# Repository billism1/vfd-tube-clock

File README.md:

# VFD Tube Clock

This project is a WiFi-connected clock that uses an IV-21 VFD (Vacuum Fluorescent Display) tube for the display and a custom PCB controlled by an ESP32 microcontroller. Built with PlatformIO using the Arduino framework, it should work with other ESP32 variants and Arduino-compatible MCUs.

## Design Overview

The PCB is designed around the Seeeduino ESP32-C3 devboard but can be adapted for other microcontrollers. The schematic and PCB design files were created using KiCad 9.0, with firmware development in VS Code with PlatformIO.

## Project Background

This is the first time I've had PCBs printed. I've been a software developer for many years and have been dabbling in electronics as a hobby over the past couple of years. I've been fascinated by vintage display technology - there's something captivating about the warm glow and classic look of old tube displays, plus those beautiful colors that display tubes like Nixie tubes and VFDs produce. I love the idea of bridging old and new technology by controlling these vintage displays with modern microcontrollers and WiFi connectivity.

**Current Status:** I'm actively refining the PCB design based on initial testing. The photos and videos below show the first prototype batch of 5 PCBs, while the KiCad files reflect ongoing improvements to the design.

## Project Photos

<div align="center">

</div>

## Web Interface

Though most of the source code I wrote myself, one of my weak areas is web UI design. I used an LLM (claude.ai) to generate a Soviet themed web UI for controlling the clock over WiFi. Soviet - because these IV-21 VFD tubes were manufactured in Soviet USSR.

**[View Web Interface Screenshots in images dir →](images/)**

## Video

*Click to watch the demo video*

## How VFD Tubes Work

VFDs use phosphor materials, typically zinc oxide (ZnO) doped with zinc sulfide or other compounds, that emit light when struck by electrons from a heated filament cathode. The phosphor coating on the anode segments converts the electron energy into visible light, usually producing a characteristic blue-green glow, though the exact color depends on the specific phosphor formulation. The IV-21 specifically uses a zinc-based phosphor that creates its distinctive aqua-blue appearance.

The electrical requirements involve multiple voltages: a low filament voltage to heat the cathode (~2.5V DC for the IV-21), and higher anode/grid voltages to accelerate electrons toward the phosphor-coated segments (typically ~27V DC for the IV-21).

Multiplexing is the key technique that makes multi-digit VFD clocks practical - instead of driving all digits simultaneously (which would require complex, expensive circuitry), we rapidly cycle through each digit position, lighting only one at a time. By switching between digits faster than your eye can detect (typically 100Hz or higher), each digit appears continuously lit even though it's only powered for a fraction of the time. This creates the illusion of a stable, solid display across all digits while dramatically simplifying the driver electronics.

## Key Circuit Design Components

### Voltage Booster Circuit
The VFD needs 27V but our power supply only provides 5V, so we need a boost converter to step up the voltage. This circuit works like a voltage pump - it stores energy in an inductor coil when a transistor switches on, then releases that energy at a higher voltage when the transistor switches off. A diode ensures the boosted voltage flows in the right direction, and the ESP32 generates the rapid on/off switching signal (PWM) that makes it all work.
The circuit takes our 5V input and pumps it up to the 27V needed by the MAX6921 driver chip, which then distributes power to light up the VFD segments.

### MAX6921 VFD Driver
The MAX6921 IC serves as the interface between the microcontroller and VFD tube. It receives 3 bytes of data from the ESP32 telling it which segments to illuminate, then distributes the boosted 27V to the appropriate pins at precise timing intervals for proper message display. Multiple MAX6921s can be chained together for tubes with more digits or multiple tubes.

## Software Features

### Core Functionality
- **WiFi Connectivity:** Automatic connection to configured network
- **NTP Time Sync:** Retrieves accurate time from "pool.ntp.org"
- **Web Server:** Built-in HTTP server for device control
- **Multiple Display Modes:**
  - Time display mode
  - Custom message mode
  - "Flash message" mode with glitchy visual effects

### Flash Message Mode
As a novelty feature (which can be disabled), the clock occasionally displays random words that appear to "glitch" into existence—brief flashes of random characters before settling on the final message for a brief period, creating a subliminal effect. The word selection (easily changed in code) and styling pay homage to the Soviet heritage of these VFD tubes.

## Planned Improvements

### Hardware Enhancements
- **Better Voltage Regulation**
- **Multi-digit Support:** Extend design for tubes with more digits (IV-27 with 13 digits)

### Software Features
- **Better Wifi Management:** Default to AP mode for after compilation WiFi configuration
- **Text Scrolling:** Support for messages longer than 8 characters
- **Smart PWM Control:** Implement PID algorithm for voltage regulation
- **Enhanced Web UI:** Additional control options and settings
- **Button Integration:** Assign meaningful functions to hardware buttons which are not programmed to do anything currently

## Acknowledgments

This project was heavily inspired by and references the excellent work of:

- **[Tiny IV-21 VFD Clock](https://hackaday.io/project/167749-tiny-iv-21-vfd-clock)** - Original design inspiration. At least this was the first similar project that I came across. Uses an Atmega328P microcontroller and external (to the microcontroller module) RTC (real-time clock) component.
- **[Tiny IV-21 VFD Clock with ESP32](https://hackaday.io/project/202799-tiny-iv-21-vfd-clock-with-esp32)** - ESP32 implementation inspired from the above mentioned "Tiny IV-21 VFD Clock" project. Excludes the external RTC component and uses WiFi/Internet for automatic time synchronization.

Special thanks to the creators of these projects for sharing their knowledge and making this hobby accessible to others.

## Project Organization

### Where to find stuff
- [Main board PCB KiCad design files](./pcb/main-board/)
- [Sub-board PCB (VFD tube holder) design files](./pcb/sub-board/)
- [Main board PCB gerber files (ready to print PCBs)](./pcb-fab/gerber-main-board/)
- [An interactive BOM (Bill of Materials) for the main board](./pcb-fab/gerber-main-board/bom/)
- [Sub-board PCB - VFD tube holder (ready to print PCBs)](./pcb-fab/gerber-sub-board/)
- [Source code](./firmware/) (Built with PlatformIO for simplified dependency management and cross-platform development)

## License

This project is licensed under the MIT License - see the [LICENSE](LICENSE) file for details.

## Contributing

Contributions are welcome! Please feel free to submit pull requests or open issues for bugs and feature requests.

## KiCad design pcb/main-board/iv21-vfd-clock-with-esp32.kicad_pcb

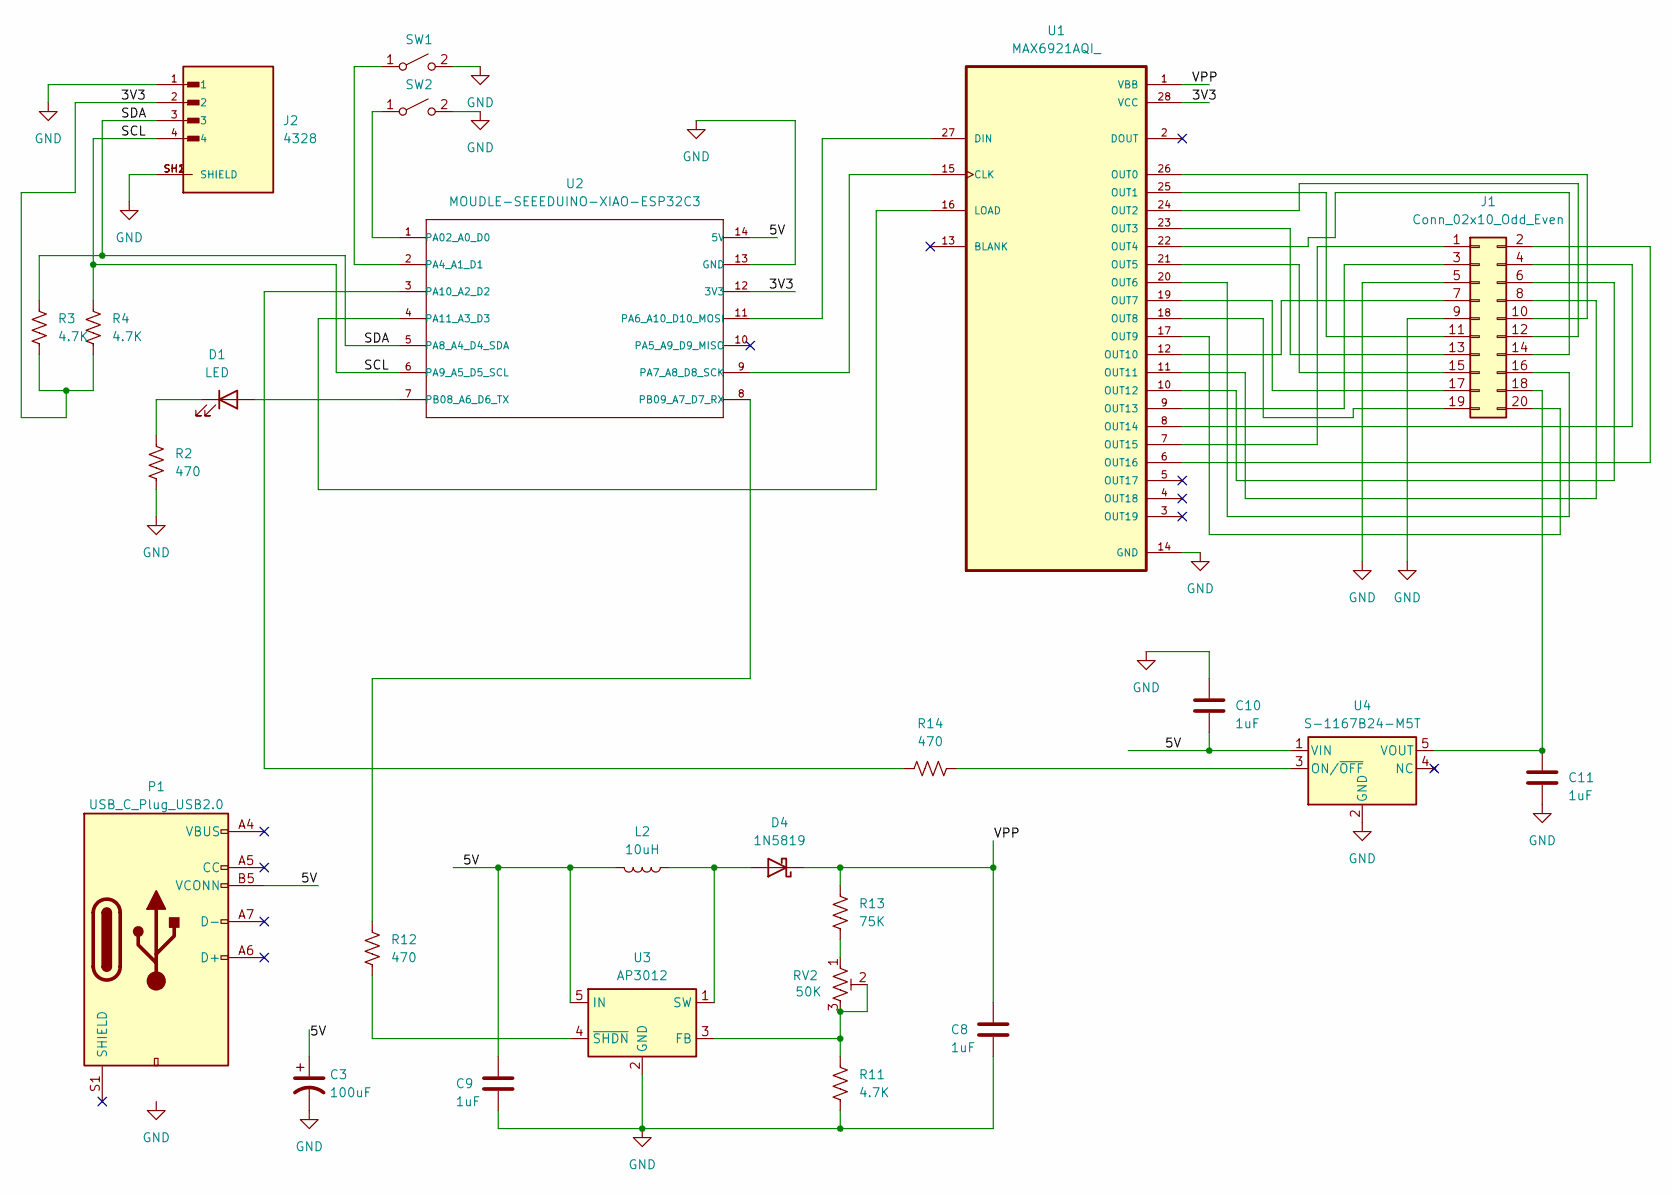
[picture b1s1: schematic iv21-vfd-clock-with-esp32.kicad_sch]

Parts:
C3: 100uF; CP_Elec_8x10.5; Voltage Rating 35V DC
C8, C9, C10, C11: 1uF; R_0805_2012Metric_Pad1.20x1.40mm_HandSolder
D1: LED; LED_1206_3216Metric
D4: 1N5819; D_SOD-123
J1: Conn_02x10_Odd_Even; PinHeader_2x10_P2.54mm_Vertical
J2: 4328; ADAFRUIT_4328; PARTREV 23/3/21
L2: 10uH; L_Radial_D7.5mm_P3.50mm_Fastron_07P
P1: USB_C_Plug_USB2.0; USB_C_Receptacle_GCT_USB4105-xx-A_16P_TopMnt_Horizontal
R2, R12, R14: 470; R_0805_2012Metric_Pad1.20x1.40mm_HandSolder
R3, R4, R11: 4.7K; R_0805_2012Metric_Pad1.20x1.40mm_HandSolder
R13: 75K; R_0805_2012Metric_Pad1.20x1.40mm_HandSolder
RV2: 50K; Potentiometer_Vishay_T93XA_Horizontal
SW1, SW2: SW_SPST; SW_Tactile_SPST_Angled_PTS645Vx58-2LFS
U1: MAX6921AQI_; PLCC127P1244X1244X457-28N; DIGI-KEY_PART_NUMBER MAX6921AQI+-ND
U2: MOUDLE-SEEEDUINO-XIAO-ESP32C3; MOUDLE14P-SMD-2.54-21X17.8MM (With Through Holes)
U3: AP3012; SOT-23-5
U4: S-1167B24-M5T; SOT-23-5

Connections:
/3V3: J2.2, R3.2, R4.2, U1.28 (VCC), U2.12 (3V3)
/5V: C3.1, C9.1, C10.2, L2.2, P1.B5 (VCONN), U2.14 (5V), U3.5 (IN), U4.1 (VIN)
/SCL: J2.4, R4.1, U2.6 (PA9_A5_D5_SCL)
/SDA: J2.3, R3.1, U2.5 (PA8_A4_D4_SDA)
/VPP: C8.1, D4.1 (K), R13.1, U1.1 (VBB)
GND: C3.2, C8.2, C9.2, C10.1, C11.2, J1.5, J1.9, J2.1, J2.SH1 (SHIELD), J2.SH2 (SHIELD), P1.A12 (GND), P1.B12 (GND), R2.2, R11.2, SW1.2 (B), SW2.2 (B), U1.14 (GND), U2.13 (GND), U3.2 (GND), U4.2 (GND)
unnamed: D1.2 (A), U2.7 (PB08_A6_D6_TX)
unnamed: D1.1 (K), R2.1
unnamed: D4.2 (A), L2.1, U3.1 (SW)
unnamed: J1.1, U1.7 (OUT15)
unnamed: J1.2, U1.6 (OUT16)
unnamed: J1.3, U1.9 (OUT13)
unnamed: J1.4, U1.8 (OUT14)
unnamed: J1.6, U1.10 (OUT12)
unnamed: J1.7, U1.12 (OUT10)
unnamed: J1.8, U1.11 (OUT11)
unnamed: J1.10, U1.26 (OUT0)
unnamed: J1.11, U1.25 (OUT1)
unnamed: J1.12, U1.24 (OUT2)
unnamed: J1.13, U1.23 (OUT3)
unnamed: J1.14, U1.22 (OUT4)
unnamed: J1.15, U1.21 (OUT5)
unnamed: J1.16, U1.20 (OUT6)
unnamed: J1.17, U1.19 (OUT7)
unnamed: C11.1, J1.18, U4.5 (VOUT)
unnamed: J1.19, U1.18 (OUT8)
unnamed: J1.20, U1.17 (OUT9)
unnamed: R13.2, RV2.1
unnamed: SW1.1 (A), U2.2 (PA4_A1_D1)
unnamed: SW2.1 (A), U2.1 (PA02_A0_D0)
unnamed: U1.15 (CLK), U2.9 (PA7_A8_D8_SCK)
unnamed: U1.27 (DIN), U2.11 (PA6_A10_D10_MOSI)
unnamed: U1.16 (LOAD), U2.4 (PA11_A3_D3)
unnamed: R14.2, U2.3 (PA10_A2_D2)
unnamed: R12.1, U2.8 (PB09_A7_D7_RX)
unnamed: R11.1, RV2.2, RV2.3, U3.3 (FB)
unnamed: R12.2, U3.4 (~SHDN)
unnamed: R14.1, U4.3 (ON/~OFF)

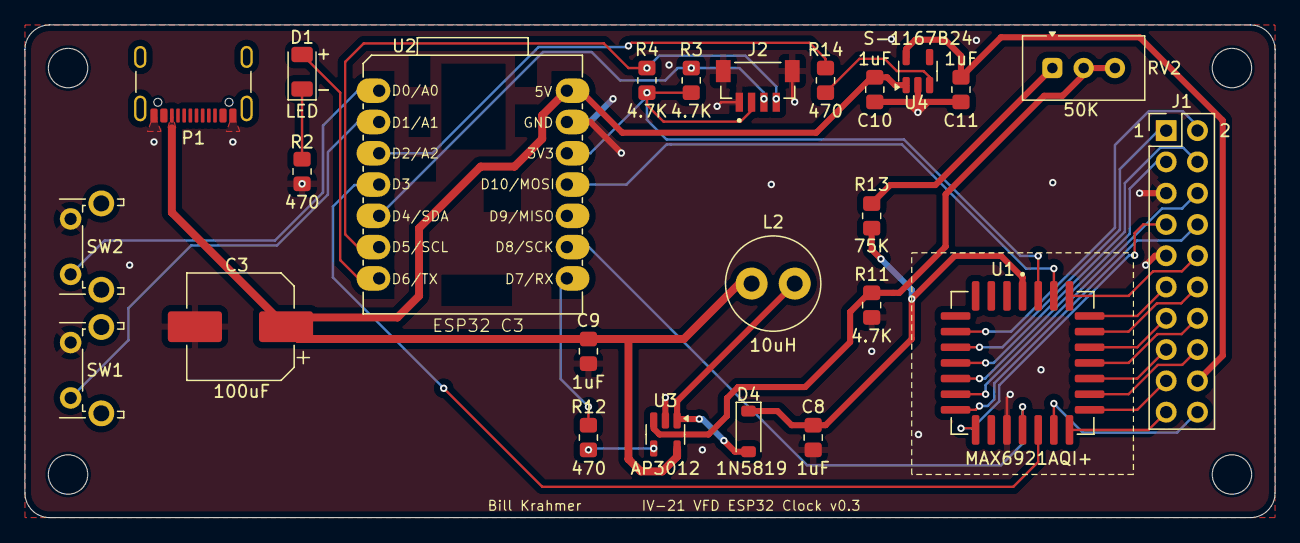
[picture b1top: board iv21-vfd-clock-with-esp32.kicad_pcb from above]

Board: 2 copper layers, 101.5 x 40.0 mm, 25 parts (0 on the bottom side), 38 nets.

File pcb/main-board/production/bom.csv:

Designator,Footprint,Quantity,Value,LCSC Part #
"C10, C11, C8, C9",0805,4,1uF,
C3,CP_Elec_8x10.5,1,100uF,
D1,1206,1,LED,
D4,D_SOD-123,1,1N5819,
J1,PinHeader_2x10_P2.54mm_Vertical,1,Conn_02x10_Odd_Even,
J2,ADAFRUIT_4328,1,4328,
L2,L_Radial_D7.5mm_P3.50mm_Fastron_07P,1,10uH,
P1,USB_C_Receptacle_GCT_USB4105-xx-A_16P_TopMnt_Horizontal,1,USB_C_Plug_USB2.0,
"R11, R3, R4",0805,3,4.7K,
"R12, R2",0805,2,470,
R13,0805,1,47K,
RV2,Potentiometer_Vishay_T93XA_Horizontal,1,50K,
"SW1, SW2",SW_Tactile_SPST_Angled_PTS645Vx58-2LFS,2,SW_SPST,
U1,PLCC127P1244X1244X457-28N,1,MAX6921AQI_,
U2,MOUDLE14P-SMD-2.54-21X17.8MM (With Through Holes),1,MOUDLE-SEEEDUINO-XIAO-ESP32C3,
U3,SOT-23-5,1,AP3012,
U4,SOT-23-5,1,S-1167B24-M5T,

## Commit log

2025-06-15 Initial "public" commit of working project.
2025-06-15 Update readme file.
2025-06-16 PDF of schematic.
2025-06-16 Update interactive BOM file.
2025-06-16 pdfs. move some seeeduino text.
2025-06-16 Updating PCB PDFs
2025-06-16 Add pdfs (#1)
    * pdfs. move some seeeduino text.
    * Updating PCB PDFs
2025-06-18 Fixed rounded corner to match other rounded corner.
2025-06-19 Voltage regulation update.
2025-06-19 Move USB-C port closer to edge of board. Move USB-C port schematic symbol to inside of drawing border.
2025-06-19 - Add details to electrolytic capacitor components. - No-fill zone for inductor footprint
2025-06-19 Update some footprints and symbols in schematic.
2025-06-20 Change inductor footprint.
2025-06-20 Some components PCB rearanging.
2025-06-21 Remove auto-save file.
2025-06-21 Add file to .gitignore
2025-06-21 Extract dad's voltage regulator symbol.
2025-06-21 Fix project library paths.
2025-06-21 Add voltage regulator schematic symbol from dad.
2025-06-21 Add some grounding vias.
2025-06-21 Some rule validation adjustments.
2025-06-21 Schematic updates for VPP.
2025-06-21 Resolve design rule checker validation errors - mostly with grounding.
2025-06-22 - Widen width of power traces. (Need to reroute one of the voltage regulators, still) - Update voltage regulator datasheet and product URL.
2025-06-22 Adjust p ower traces.
2025-06-22 - Update power traces - Add in-series resistor with VPP voltage divider trim pot.
2025-06-22 Change fabrication output dir and use fabricaiton tookit plugin to genreate gerber.
2025-06-22 Fix some silkmask labels for trim pot.
2025-06-24 Fabrication files update.
2025-06-24 Some trace updates.
2025-06-24 change resistor value.
2025-06-26 Add 470R resistor to S-1167B24 on/off pin
2025-08-18 Fixed LEDC functionc calls. Using ledcSetup() and ledcAttachPin() functions instead of ledcAttach().
    While using this version of the LEDC lib, the channel number is passed into ledcWrite() instead of the pin number.
2025-08-18 Renamed readme file.
2025-08-18 Initial REST API suport for Home Assistant.
2025-08-18 Update IPs in docs.
2025-08-18 Debug button presses.
2025-08-18 /status returns button state as well, now.
2025-08-19 Fix fialment toggle via HA.
2025-08-19 Expose FlashMessagesToggle
2025-08-19 actual_voltage report to HA.
2025-08-19 Fixing voltage boost pwm
2025-08-19 use the older (more precise) pwm resolution.
2025-08-19 Adjust target voltage to 27V and update boost duty cycle reporting in status response
2025-08-20 Remove unused yaml.
2025-08-20 Make Home Assistant functionality optional with a build flag.
2025-08-20 Make flash message a little less frequent.
2025-08-20 Add home assistant functionality (#4)
    * Renamed readme file.
    * Initial REST API suport for Home Assistant.
    * Update IPs in docs.
    * Debug button presses.
    * /status returns button state as well, now.
    * Fix fialment toggle via HA.
